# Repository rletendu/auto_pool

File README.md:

# AutoPool

ESP32 swimming-pool controller with pH / ORP / filter automation, Nextion touch UI, web dashboard, MQTT, and native Home Assistant autodiscovery.

AutoPool runs unattended on the side of the pool: it schedules the filter pump, doses chlorine on ORP, holds pH inside a target band by injecting acid (and optionally base) through peristaltic pumps, watches tank levels, and exposes everything over a 5″ touch panel, a web UI, and MQTT.

---

## Table of contents

- [Features](#features)
- [Hardware](#hardware)
- [Architecture](#architecture)
- [Build, flash and first boot](#build-flash-and-first-boot)
- [Configuration](#configuration)
- [Winter mode](#winter-mode)
- [MQTT](#mqtt)
- [Home Assistant integration](#home-assistant-integration)
- [Web UI and Nextion display](#web-ui-and-nextion-display)
- [OTA, CLI and Telnet](#ota-cli-and-telnet)
- [ESPHome alternative](#esphome-alternative)
- [Repository layout](#repository-layout)
- [Credits and license](#credits-and-license)

---

## Features

**Regulation**
- Filter pump scheduling — 24-hour fixed bitmap or per-temperature program (selected by `filter_auto_mode`)
- Filter speed control (FULL / REG) on a variable-speed pump
- Periodic short-cycle filter run for stagnation prevention
- **Winter mode** — short winter filter program, frost protection driven by an outdoor temperature pushed by Home Assistant, chemistry locked OFF (see [Winter mode](#winter-mode))
- pH minus (and optional pH plus) dosing on a fixed regulation cycle, proportional to deviation from target
- ORP / chlorine dosing on a fixed regulation cycle with daily mL caps
- Daily injection counters with automatic midnight reset (preserved across soft resets via RTC slow memory)

**Sensing**
- DS18B20 — water temperature (OneWire)
- DHT22 — air temperature and humidity inside the enclosure
- ADS1115 — pH probe, ORP probe, and pump-loop pressure transducer (3 channels)
- DS3231 — battery-backed RTC
- Four float switches — water level + Cl / pH- / pH+ tank levels

**Interfaces**
- Nextion 5″ resistive touch panel (`hmi/auto_pool_ui.HMI`)
- Responsive web dashboard served from SPIFFS (`http://<ip>/`)
- MQTT — measures, states, parameters, log, command, with **Home Assistant autodiscovery** (~40 entities) and LWT availability
- Serial CLI (`SimpleCLI`)
- OTA — firmware, SPIFFS filesystem, and Nextion display

---

## Hardware

The full schematic and PCB live in [`hardware/`](hardware/):

- [`hardware/autopool.pdf`](hardware/autopool.pdf) — schematic
- [`hardware/autopool.kicad_pcb`](hardware/autopool.kicad_pcb) — KiCad PCB
- [`hardware/autopool.png`](hardware/autopool.png), [`autopool_3.png`](hardware/autopool_3.png) — board renders
- [`3D/`](3D/) — printable enclosure parts (STL / STEP)

### Bill of materials (top level)

| Block | Part |
|---|---|
| MCU | ESP32 dev module |
| Display | Nextion 5″ (NX8048T050 or compatible) |
| Analog frontend | ADS1115 (I²C) for pH / ORP / pressure |
| RTC | DS3231 (I²C, battery-backed) |
| Air sensor | DHT22 |
| Water sensor | DS18B20 (OneWire) |
| Filter pump driver | Solid-state relay (active-high) |
| Dosing | 3× peristaltic pumps (Cl, pH-, pH+) on relays (active-low) |
| Levels | 4× float switches (water, Cl, pH-, pH+) |
| Misc | Piezo buzzer, two status LEDs |

### Pin map (excerpt, see [`src/board.h`](src/board.h) for the source of truth)

| Function | GPIO | Notes |
|---|---|---|
| Filter pump SSR | `PIN_EXT1` (14) | active **high** (`PUMP_FILTER_ACTIVE_VALUE = true`) |
| Filter speed (FULL/REG) | `PIN_EXT2` (15) | optional, gated by `HAS_FILTER_PWR_CTRL` |
| Cl pump relay | 25 | active **low** (`PUMP_ACTIVE_VALUE = false`) |
| pH- pump relay | 32 | active low |
| pH+ pump relay | 4 | active low, gated by `HAS_PH_PLUS_PUMP` |
| DS18B20 (water temp) | 13 | OneWire |
| DHT22 | 18 | |
| I²C (ADS1115, DS3231) | 21 / 22 | SDA / SCL |
| Nextion display | 16 / 17 | `Serial2` RX / TX, 115 200 baud |
| Float switches | 34, 35, 36, 39 | water / Cl / pH- / pH+ (input-only pins) |
| Buzzer | 5 | |

> **Polarity matters.** The filter pump SSR is wired through `PIN_EXT1` and is active-high; the dosing relays are active-low. Always go through the helpers in `board.h` (`pump_filtration_on/off`, `pump_ph_minus_on/off`, …) — never `digitalWrite` directly from feature code.

---

## Architecture

```
                    ┌────────────────────────┐
                    │       main.cpp         │
                    │  setup() / loop()      │
                    └──────────┬─────────────┘
                               │ SoftTimer ticks
        ┌──────────────┬───────┴───────┬──────────────┐
        ▼              ▼               ▼              ▼
  filter_control   ph_control     orp_control     measures
   (state machine) (state machine)(state machine) (sensor reads)
        │              │               │              │
        └────────┬─────┴────────┬──────┴──────┬───────┘
                 ▼              ▼             ▼
              board.h        state.h     parameters.h
            (HW helpers)   (live state)  (persisted setpoints)
                 │              │             │
                 ▼              ▼             ▼
        ┌────────────────────────────────────────────┐
        │   display  │  mqtt  │  server  │  cli  │ ota │
        └────────────────────────────────────────────┘
```

- **Cooperative scheduling** — every subsystem registers periodic work on a [`SoftTimer`](src/soft_timer.h) instance; no `delay()` in the main loop.
- **Three regulators** with explicit state machines defined in [`src/state.h`](src/state.h):
  - `filter_control_state_t` — IDLE → WARM_UP → ACTIVE → EXTENDED → PERIODIC, plus FROST (winter-mode frost protection)
  - `ph_control_state_t` — IDLE / MINUS_INJECTION_{ON,OFF} / PLUS_INJECTION_{ON,OFF}
  - `orp_control_state_t` — IDLE / INJECTION_{ON,OFF}
- **Persistence** — two SPIFFS JSON files in [`data/`](data/):
  - `/config.json` ↔ `ParametersStruture` ([`src/parameters.h`](src/parameters.h))
  - `/state.json` ↔ last-known mode of each regulator, winter mode and the pre-winter chemistry modes (so a reboot does not reset operator intent)
- **Compile-time feature gates** in [`src/config.h`](src/config.h): `HAS_PH_CONTROL`, `HAS_ORP_CONTROL`, `HAS_FILTER_CONTROL`, `HAS_FILTER_PWR_CTRL`, `HAS_PH_PLUS_PUMP`, `HAS_MQTT`, `HAS_OTA`, `HAS_WEB_SERVER`, `HAS_CLI`, `HAS_TELNET_SERVER`, `HAS_QUIET_MEASURES`, `HAS_CUSTOM_MAC`.

---

## Build, flash and first boot

PlatformIO is the only toolchain. The single environment is `esp32dev`, defined in [`platformio.ini`](platformio.ini).

```bash
# Build
pio run

# Flash firmware over USB
pio run -t upload

# Flash firmware OTA
pio run -t upload --upload-port 192.168.x.x

# Flash the SPIFFS filesystem (web UI + config.json + state.json)
# Required after editing anything under data/
pio run -t uploadfs

# Serial monitor at 115 200 baud
pio device monitor

# Clean build
pio run -t clean
```

> **Firmware vs. filesystem are two independent flashes.** `pio run -t upload` writes the application binary (everything compiled from `src/`); `pio run -t uploadfs` writes the SPIFFS image built from `data/` (web UI, `config.json`, `state.json`). They're independent partitions on the ESP32 — flashing one never touches the other. Rules of thumb:
>
> - **Edited C/C++ in `src/` or `lib/`** → `pio run -t upload`. No `uploadfs` needed; settings and web assets are untouched.
> - **Edited anything under `data/`** (web UI, default `config.json`) → `pio run -t uploadfs`. No firmware reflash needed.
> - **Both** → run them in either order; e.g. `pio run -t upload && pio run -t uploadfs`.
> - **OTA**: both targets accept `--upload-port <ip>` to flash over Wi-Fi via `espota`, e.g. `pio run -t uploadfs --upload-port 192.168.x.x`.
> - **Heads up on `uploadfs`**: it rewrites the whole SPIFFS partition, including `config.json` **and** `state.json`. Settings changed via the web UI / portal / MQTT are lost, and the default `data/state.json` puts pH / ORP back in AUTO, drops winter mode and resets the total filter runtime. Pull the live config back first (`curl http://<ip>/getparameters > data/config.json`) if you want to preserve it.
> - **Updating only the web UI** on a running controller: skip `uploadfs` and push the changed files through the built-in file upload endpoint, which leaves `config.json` / `state.json` alone:
>   ```bash
>   for f in index.html app.js settings.html settings.js style.css; do
>     curl -F "file=@data/$f;filename=/$f" http://<ip>/edit
>   done
>   ```

> **There are no unit tests** wired up. `test/autopool_tester.py` is a host-side helper, not a PlatformIO test runner.

### First boot

On first power-up the device opens a captive Wi-Fi portal named **`AUTOPOOL_CONFIG`**. Connect to it and configure:

- Wi-Fi SSID / password
- MQTT server / port / user / password
- MQTT base topic (default: `autopool`)

Settings persist to `/config.json` on SPIFFS. To re-trigger the portal later, send the `portal` CLI command on the serial console, or hit `/reboot` after wiping settings via `portal_reset`.

---

## Configuration

Three editing channels feed the same [`ParametersStruture`](src/parameters.h):

1. **Web UI** — `http://<ip>/settings.html` (form is bound by [`data/settings.js`](data/settings.js))
2. **MQTT** — publish a full JSON payload to `<base>/CMD/PARAMETERS`, or update one field at a time with `<base>/CMD/SET/<KEY>` *(see [MQTT](#mqtt))*
3. **WiFiManager portal** — for the network and broker fields only, on first boot or after `portal` / `portal_reset`

### Most-edited parameters

| Field | Meaning | Typical |
|---|---|---|
| `target_ph`, `delta_ph` | pH setpoint and dead-band | 7.4 ± 0.15 |
| `target_orp`, `delta_orp` | ORP setpoint (mV) and dead-band | 650 ± 70 |
| `flow_cl`, `flow_ph_minus`, `flow_ph_plus` | Peristaltic pump flow rate (mL/min) | 25 |
| `cl_max_day`, `phm_max_day` | Daily injection caps (mL) | 2000 |
| `pressure_warning` | Filter loop alarm threshold (bar) | 1.9 |
| `ph_offset`, `orp_offset` | Probe calibration offsets | 0 |
| `timer_prog` | 24-bit hourly bitmap for filter run | — |
| `filter_auto_mode` | `0` = bitmap, `1` = function of water temperature | 0 |
| `timer_prog_temperature[11]` | Per-temperature bitmaps (10 °C → 30 °C, step 2 °C) | — |
| `periodic_filter_time` | Minutes between short anti-stagnation cycles (0 disables) | 0 |
| `winter_start_hour`, `winter_duration_h` | Winter filter window (start hour, length in hours, wraps past midnight) | 4, 3 |
| `frost_threshold` | Outdoor temperature (°C) that starts frost protection in winter mode | 1.0 |
| `ha_discovery_enabled`, `ha_discovery_prefix` | HA autodiscovery toggle and topic prefix | `false`, `homeassistant` |

---

## Winter mode

An *active* wintering mode: the water stays in the pool, the filter runs a short daily window and protects the pipes from freezing. It is toggled from Home Assistant (`switch.autopool_winter_mode`), the web dashboard, or MQTT `SET/WINTER_MODE`, and persists across reboots. The Nextion HMI is unchanged: it shows the winter program in the timer grid and the events on the LOG page.

While winter mode is on:

- **Filtration** — the AUTO program is replaced by `winter_duration_h` hours starting at `winter_start_hour` (default 04:00–07:00). `filter_auto_mode` and `timer_prog` are left untouched and apply again when winter mode ends.
- **Chemistry** — pH-, pH+ and ORP are forced OFF; any request to switch them back on (Nextion, MQTT, web, CLI) is refused and logged. Their previous modes are saved and restored when winter mode ends.
- **Frost protection** — in filter AUTO, the pump runs continuously (filter state `FROST`) when the outdoor temperature drops to `frost_threshold`, and stops 1.5 °C above it.
  - The outdoor temperature is pushed by Home Assistant to `<base>/CMD/OUTDOOR_TEMP`. A value older than 30 min is ignored, and the controller falls back to the water temperature (frost below 4 °C, cleared above 5 °C).
  - The enclosure DHT22 is **not** used: it reads the temperature inside the box.
  - A manual filter **OFF** always wins (maintenance): the pump is not started, but `frost_alert` is raised instead.

Home Assistant has to feed the outdoor temperature. An automation such as the following works: every 10 minutes and on each change, it publishes the coldest of a garden sensor and the weather forecast.

```yaml
alias: AutoPool – Outdoor temperature
mode: queued
triggers:
  - trigger: state
    entity_id: sensor.garden_temperature
  - trigger: state
    entity_id: weather.home
    attribute: temperature
  - trigger: time_pattern
    minutes: /10
  - trigger: homeassistant
    event: start
variables:
  outdoor_temps: >-
    {{ [states('sensor.garden_temperature'), state_attr('weather.home', 'temperature')]
       | select('is_number') | map('float') | list }}
conditions:
  - condition: template
    value_template: "{{ outdoor_temps | count > 0 }}"
actions:
  - action: mqtt.publish
    data:
      topic: autopool/CMD/OUTDOOR_TEMP
      payload: "{{ outdoor_temps | min | round(1) }}"
```

---

## MQTT

All topics are rooted at `<base>` (the value of `mqtt_base_topic`, default `autopool`).

### Published

| Topic | Retained | Payload |
|---|---|---|
| `<base>/AVAIL` | yes | `online` while the controller is up; `offline` published as LWT on disconnect |
| `<base>/MEAS` | no | JSON snapshot of [`MeasuresStructure`](src/measures.h) (temps, pH, ORP, pressure, levels, daily mL counters, filter runtime, boot count). `water_temperature` is omitted until the first valid reading after boot, and `outdoor_temperature` while it is stale |
| `<base>/STATE_FILTER` | no | JSON snapshot of the filter regulator state, including `winter_mode`, `frost_active`, `frost_alert` |
| `<base>/STATE_PH` | no | JSON snapshot of the pH± regulator state |
| `<base>/STATE_ORP` | no | JSON snapshot of the ORP regulator state |
| `<base>/PARAM` | no | Echo of the current `ParametersStruture` after any change |
| `<base>/LOG`, `<base>/DEBUG` | no | Free-form text |
| `<prefix>/+/autopool_<mac>/+/config` | yes | HA discovery configs (only when `ha_discovery_enabled` is set) |

### Subscribed (`<base>/CMD/<KEY>`)

**Mode commands** *(legacy string suffix, empty payload):*
`FILTER_MODE_AUTO` · `FILTER_MODE_ON` · `FILTER_MODE_OFF` · `FILTER_PWR_FULL` · `FILTER_PWR_REG` · `ORP_MODE_AUTO` · `ORP_MODE_ON` · `ORP_MODE_OFF`

**Per-field SET commands** *(payload = scalar value, suitable for HA selects/numbers):*

| Topic | Payload |
|---|---|
| `SET/FILTER_MODE` | `AUTO` \| `ON` \| `OFF` |
| `SET/FILTER_POWER` | `FULL` \| `REG` |
| `SET/ORP_MODE` | `AUTO` \| `ON` \| `OFF` |
| `SET/PH_MINUS_MODE` | `AUTO` \| `ON` \| `OFF` |
| `SET/PH_PLUS_MODE` | `AUTO` \| `ON` \| `OFF` |
| `SET/TARGET_PH`, `SET/DELTA_PH` | float |
| `SET/TARGET_ORP`, `SET/DELTA_ORP` | float (mV) |
| `SET/FLOW_CL`, `SET/FLOW_PH_MINUS`, `SET/FLOW_PH_PLUS` | float (mL/min) |
| `SET/CL_MAX_DAY`, `SET/PHM_MAX_DAY` | float (mL) |
| `SET/PRESSURE_WARNING` | float (bar) |
| `SET/PH_OFFSET`, `SET/ORP_OFFSET` | float (calibration) |
| `SET/PERIODIC_FILTER_TIME` | minutes |
| `SET/WINTER_START_HOUR`, `SET/WINTER_DURATION_H` | integer (hour 0–23, hours 0–24) |
| `SET/FROST_THRESHOLD` | float (°C) |

Per-field SET commands persist to `/config.json` and echo on `<base>/PARAM`.

**Winter mode:**

| Topic | Payload |
|---|---|
| `SET/WINTER_MODE` | `ON` \| `OFF` — persisted in `/state.json` |
| `OUTDOOR_TEMP` | float (°C), pushed periodically by HA; volatile, stale after 30 min |

**JSON updates** *(payload = full JSON document):*
`PARAMETERS` · `MEASURES` · `FILTER_STATE` · `ORP_STATE` · `PH_STATE`

**Utility:** `RESET` · `RST_DAILY_ML_ORP` · `BEEP` · `GET_PARAMETERS` · `GET_STATES` · `LOG` · `FS`

---

## Home Assistant integration

Two paths, pick one.

### Autodiscovery (recommended)

1. Open the AutoPool web UI → **Settings** → tick **Enable autodiscovery**, leave the prefix as `homeassistant` unless your HA instance uses a custom one.
2. Click **Submit**. The controller publishes ~55 retained discovery configs under `<prefix>/+/autopool_<mac>/+/config`.
3. Home Assistant's MQTT integration picks them up automatically. AutoPool appears as a single device with:
   - Sensors — water / system temperature, humidity, pressure, pH, ORP, daily mL counters, boot count
   - Binary sensors — water level, three tank levels, four pump-running indicators
   - Selects — filter mode, filter power, ORP mode, pH± modes
   - Switch — winter mode
   - Binary sensors — frost protection running, frost alert
   - Sensor — outdoor temperature as received from HA (diagnostic)
   - Numbers — every setpoint listed in [Configuration](#configuration), including the winter settings
   - Buttons — controller reset, daily Cl counter reset, boot counter reset
   - Diagnostic sensors — internal state of the three regulators
4. To remove the device: untick the checkbox; the controller publishes empty retained payloads to clear every discovery topic.

The companion dashboard at [`homeassistant/dashboards/autopool.yaml`](homeassistant/dashboards/autopool.yaml) is wired entirely to the autodiscovered entity_ids (`<domain>.autopool_<object>`, courtesy of the `obj_id` field in each discovery payload). It uses only stock Lovelace cards — no HACS install required. Drop it under `<HA_config>/dashboards/` and register it via the `lovelace.dashboards` block in [`homeassistant/configuration_snippet.yaml`](homeassistant/configuration_snippet.yaml).

### Multi-device deployment

Two AutoPool controllers can share a single MQTT broker and a single Home Assistant instance. Set `device_suffix` on each one — short, lowercase, `[a-z0-9_]`, max 12 chars (e.g. `north`, `south`, `pool1`). The suffix is spliced into:

| Identifier | Empty suffix | Suffix `north` |
|---|---|---|
| MQTT `client_id` | `AUTOPOOL` | `AUTOPOOL_north` |
| HA `obj_id` (entity_id slug) | `autopool_<object>` | `autopool_north_<object>` |
| HA device name | `AutoPool` | `AutoPool north` |
| WiFiManager portal SSID | `AUTOPOOL_CONFIG` | `AUTOPOOL_CONFIG_north` |
| OTA mDNS hostname | `autopool.local` | `autopool-north.local` |

`mqtt_base_topic` is also auto-rewritten when you set the suffix via `<base>/CMD/SET/DEVICE_SUFFIX` (and only if the topic still has the legacy default `autopool` / empty). Set it manually otherwise via the WiFi portal or web UI to keep the two devices on disjoint topic trees.

Caveats:
- The very first portal setup of a fresh unit always uses the legacy SSID `AUTOPOOL_CONFIG` (suffix is set inside the portal itself). Configure both units sequentially the first time, not simultaneously.
- After changing a non-empty suffix, HA's old entities go to *unavailable* until the next HA restart — the controller publishes empty retained payloads to the old discovery topics so they age out cleanly.
- The supplied dashboard at [`homeassistant/dashboards/autopool.yaml`](homeassistant/dashboards/autopool.yaml) targets a single device with empty suffix. For multi-device dashboards, copy the file and `sed 's/autopool_/autopool_<suffix>_/g'` to retarget.

### Manual packages (legacy)

If you'd rather not run discovery, the older path still works: copy [`homeassistant/packages/autopool.yaml`](homeassistant/packages/autopool.yaml) and [`homeassistant/custom_templates/autopool.jinja`](homeassistant/custom_templates/autopool.jinja) into your HA config, enable `packages: !include_dir_named packages` in `configuration.yaml`, and **disable** the autodiscovery toggle on the controller — running both at once creates duplicate entities. The header of `packages/autopool.yaml` documents the migration trade-offs.

---

## Web UI and Nextion display

### Web UI

| Dashboard | Settings |
| --- | --- |
|  |  |

The dashboard is responsive and works the same on a phone:

Served by [`src/server.cpp`](src/server.cpp) from SPIFFS:

- `/` — live dashboard (measures, daily counters, regulator modes, winter mode and frost status)
- `/settings.html` — full configuration form
- `/getmeasures`, `/getparameters`, `/getfilterstate`, `/getorpstate`, `/getphstate` — JSON endpoints used by the dashboard
- `/setparameters` — POST endpoint backing the settings form
- `/filter_auto`, `/filter_on`, `/filter_off`, `/filter_pwr_full`, `/filter_pwr_reg`, `/orp_*`, `/ph_*`, `/winter_on`, `/winter_off` — quick-action buttons
- `/reboot`, `/rst_daily_ml_orp` — maintenance
- `/edit`, `/list`, `/fs` — SPIFFS file browser

### Nextion display

- HMI source: [`hmi/auto_pool_ui.HMI`](hmi/auto_pool_ui.HMI) (open in Nextion Editor)
- Pre-built TFT firmware lives under [`hmi/tft/`](hmi/tft/) — flash directly from an SD card, or push over the air via [`src/ota_tft.cpp`](src/ota_tft.cpp) (uses [`lib/ESPNexUpload`](lib/ESPNexUpload))
- Display drives `Serial2` (`PIN_RX2 = 16`, `PIN_TX2 = 17`) at 115 200 baud
- Firmware references widgets by name in [`src/display_components.cpp`](src/display_components.cpp); add new touch callbacks in [`src/display.cpp`](src/display.cpp)

---

## OTA, CLI and Telnet

- **Firmware OTA** — ArduinoOTA, invoked via `pio run -t upload --upload-port <ip>`
- **Filesystem OTA** — same syntax with `-t uploadfs`
- **Display OTA** — streamed by `ESPNexUpload`, triggered from the web UI / MQTT
- **Serial CLI** — three commands today (parsed by `SimpleCLI` in [`src/cli.cpp`](src/cli.cpp)):
  - `portal` — open the Wi-Fi captive portal and reboot
  - `portal_reset` — wipe Wi-Fi credentials and reboot
  - `format` — format SPIFFS (destructive)
- **Telnet** — off by default (`HAS_TELNET_SERVER 0` in [`src/config.h`](src/config.h)); flips on a `RemoteDebug` server when enabled

---

## ESPHome alternative

[`autopool_esphome.yaml`](autopool_esphome.yaml) is a parallel, in-progress port of the same hardware to ESPHome. The PlatformIO firmware in [`src/`](src/) remains the authoritative implementation. Migration notes / design log: [`2026-04-24-migration_esphome.txt`](2026-04-24-migration_esphome.txt). Secrets for the ESPHome flavour go in `secrets.yaml` (gitignored).

---

## Repository layout

```
src/                   Firmware (Arduino / PlatformIO) — main.cpp + per-subsystem modules
data/                  SPIFFS payload (web UI, config.json, state.json)
lib/                   Vendored libraries: Nextion, WiFiManager, RemoteDebug, SerialDebug, ESPNexUpload
hardware/              KiCad schematic, PCB, renders, gerbers
3D/                    Enclosure parts (STL / STEP)
hmi/                   Nextion HMI source + compiled .tft + assets
homeassistant/         Drop-in HA packages, dashboard, Jinja templates, integration snippet
autopool_esphome.yaml  Experimental ESPHome rewrite
platformio.ini         Build config (single env: esp32dev)
CLAUDE.md              Architecture / contributor guide (also used by AI assistants)
```

---

## Credits and license

Author: **Raphaël Letendu** — [github.com/rletendu/auto_pool](https://github.com/rletendu/auto_pool).

Vendored library licenses live alongside each library under [`lib/*/LICENSE*`](lib/). The repository does not currently carry a top-level `LICENSE` file; if you intend to publish the firmware, add one (MIT or GPL-2.0+ are common picks for ESP32 hobby projects).

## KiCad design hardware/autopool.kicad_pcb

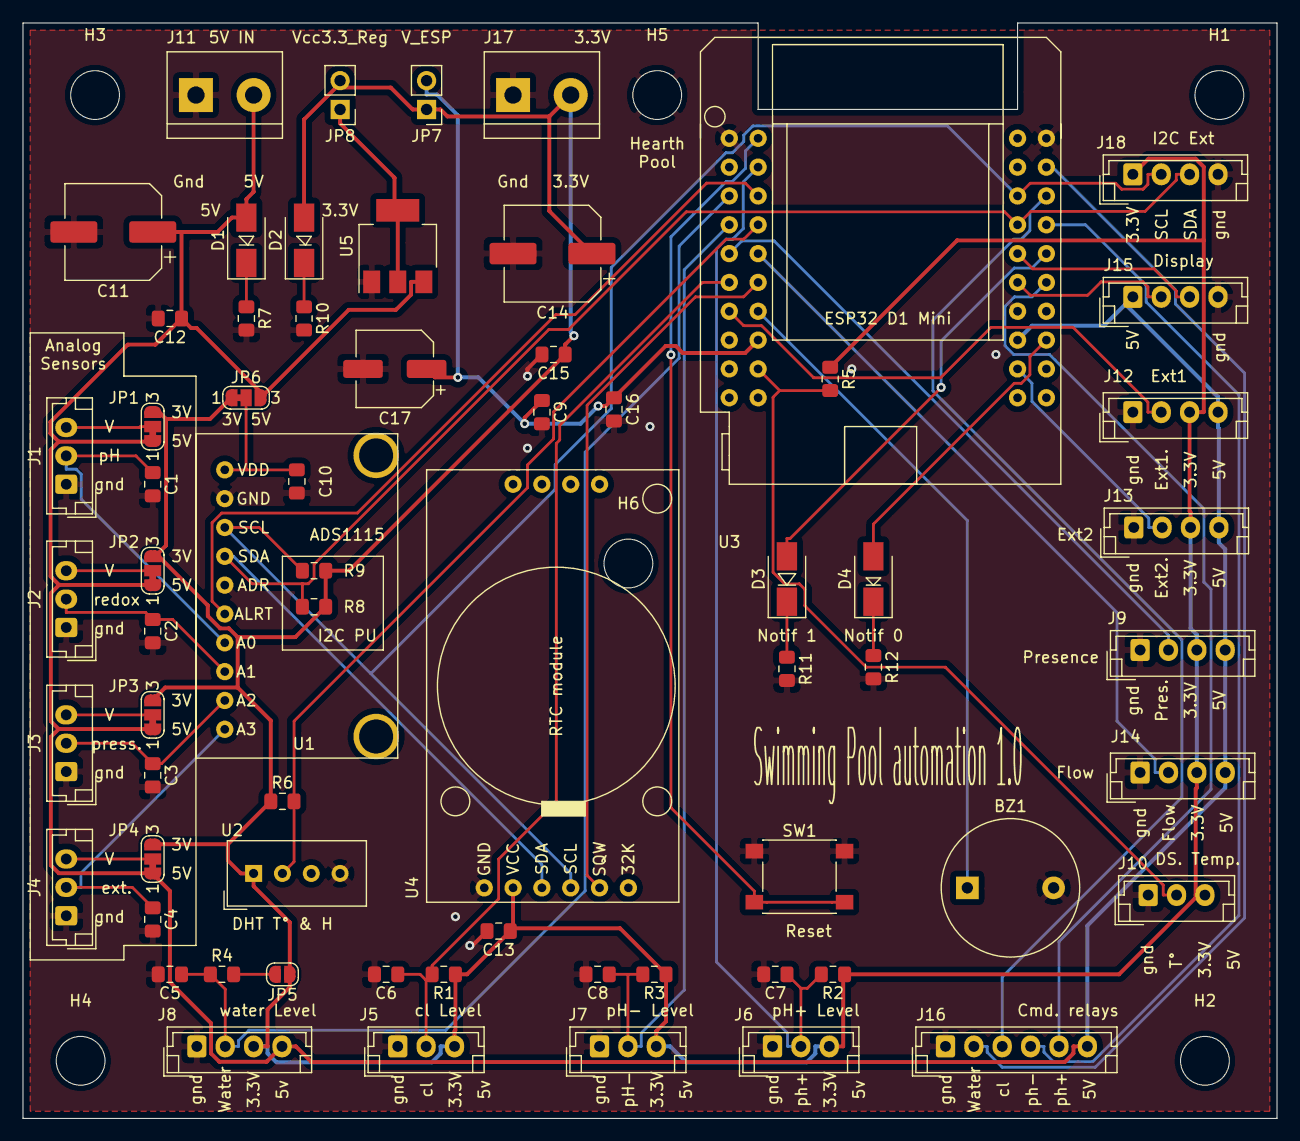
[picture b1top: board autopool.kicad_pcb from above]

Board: 2 copper layers, 110.5 x 96.5 mm, 72 parts (0 on the bottom side), 43 nets.

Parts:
BZ1: Buzzer; Buzzer_12x9.5RM7.6
C1, C2, C3, C4, C5, C6, C7, C8: 100p; C_0805_2012Metric_Pad1.15x1.40mm_HandSolder
C9, C10, C12, C13, C15: 100n; C_0805_2012Metric_Pad1.15x1.40mm_HandSolder
C11, C14: 47u; CP_Elec_8x11.9
C16: 1u; C_0805_2012Metric_Pad1.15x1.40mm_HandSolder
C17: 10u; CP_Elec_6.3x9.9
D1: 5.5V; D_SMA
D2: 3.3V; D_SMA
D3: Notif1; D_SMA
D4: Notif0; D_SMA
H1, H2, H3, H4, H5, H6: MountingHole_Pad; MountingHole_4.3mm_M4
J1: pH Sense; JST_EH_B3B-EH-A_1x03_P2.50mm_Vertical
J2: Cl Sense; JST_EH_B3B-EH-A_1x03_P2.50mm_Vertical
J3: Pressure. Sense; JST_EH_B3B-EH-A_1x03_P2.50mm_Vertical
J4: Extra Sense; JST_EH_B3B-EH-A_1x03_P2.50mm_Vertical
J5: Cl LevelMin; JST_EH_B3B-EH-A_1x03_P2.50mm_Vertical
J6: pH+ LevelMin; JST_EH_B3B-EH-A_1x03_P2.50mm_Vertical
J7: pH- LevelMin; JST_EH_B3B-EH-A_1x03_P2.50mm_Vertical
J8: Water_level; JST_EH_B4B-EH-A_1x04_P2.50mm_Vertical
J9: Presence; JST_EH_B4B-EH-A_1x04_P2.50mm_Vertical
J10: Water_temp; JST_EH_B3B-EH-A_1x03_P2.50mm_Vertical
J11: VCC_5V; TerminalBlock_bornier-2_P5.08mm
J12: Ext1; JST_EH_B4B-EH-A_1x04_P2.50mm_Vertical
J13: Ext2; JST_EH_B4B-EH-A_1x04_P2.50mm_Vertical
J14: Flow; JST_EH_B4B-EH-A_1x04_P2.50mm_Vertical
J15: Display; JST_EH_B4B-EH-A_1x04_P2.50mm_Vertical
J16: Relays; JST_EH_B6B-EH-A_1x06_P2.50mm_Vertical
J17: VCC_3.3V; TerminalBlock_bornier-2_P5.08mm
J18: I2C_est1; JST_EH_B4B-EH-A_1x04_P2.50mm_Vertical
JP1: V_pH; SolderJumper-3_P1.3mm_Bridged12_RoundedPad1.0x1.5mm_NumberL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
JP2: V_cl; SolderJumper-3_P1.3mm_Bridged12_RoundedPad1.0x1.5mm_NumberL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
JP3: V_Press.; SolderJumper-3_P1.3mm_Bridged12_RoundedPad1.0x1.5mm_NumberL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
JP4: V_extra; SolderJumper-3_P1.3mm_Bridged12_RoundedPad1.0x1.5mm_NumberL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
JP5: pu_water; SolderJumper-2_P1.3mm_Open_RoundedPad1.0x1.5mm
JP6: V_ads; SolderJumper-3_P1.3mm_Bridged12_RoundedPad1.0x1.5mm_NumberL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
JP7: vccESP; PinHeader_1x02_P2.54mm_Vertical
JP8: VCC_33; PinHeader_1x02_P2.54mm_Vertical
R1, R2, R3, R4, R5, R6: 10k; R_0805_2012Metric_Pad1.15x1.40mm_HandSolder
R7: 470; R_0805_2012Metric_Pad1.15x1.40mm_HandSolder
R8, R9: 2.2k; R_0805_2012Metric_Pad1.15x1.40mm_HandSolder
R10, R11, R12: 330; R_0805_2012Metric_Pad1.15x1.40mm_HandSolder
SW1: Reset; SW_Push_1P1T_NO_6x6mm_H9.5mm
U1: ADS1115_module
U2: DHT11; Aosong_DHT11_5.5x12.0_P2.54mm
U3: ESPMINI32; esp32_mini
U4: RTC_DS3231_MODULE; RTC_DS3231_MODULE_H
U5: AMS1117-3.3; SOT-223-3_TabPin2

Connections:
+3V3: C13.1, C14.1, C15.1, D2.2, J5.3, J6.3, J7.3, J8.3, J9.3, J10.3, J12.3, J13.3, J14.3, J17.2, J18.1, JP1.3, JP2.3, JP3.3, JP4.3, JP5.1, JP6.1, JP7.1, JP8.2, R1.1, R2.1, R3.1, R5.1, R6.1, R8.1, R9.1, U2.1, U4.2
+5V: C11.1, C12.1, D1.2, J8.4, J9.4, J11.2, J12.4, J13.4, J14.4, J15.1, J16.6, JP1.1, JP2.1, JP3.1, JP4.1, JP6.3, U3.28, U5.3
/3.3_esp: C9.1, C16.1, C17.1, JP7.2, U3.18
/3V3_reg: JP8.1, U5.2
/Cl: C2.1, J2.2, U1.8
/Press: C3.1, J3.2, U1.9
/adc_alrt: U1.6, U3.13
/buzzer: BZ1.1, U3.17
/dht: R6.2, U2.2, U3.14
/ext1: J12.2, U3.7
/ext2: J13.2, U3.29
/extra: C4.1, J4.2, U1.10
/flow: J14.2, U3.15
/led0: D4.2, U3.38
/led1: D3.2, U3.35
/levelmin_cl: C6.1, J5.2, R1.2, U3.6
/levelmin_ph+: C7.1, J6.2, R2.2, U3.12
/levelmin_ph-: C8.1, J7.2, R3.2, U3.4
/levelmin_water: C5.1, J8.2, R4.1, U3.3
/pH: C1.1, J1.2, U1.7
/presence: J9.2, U3.5
/pump_cl: J16.3, U3.33
/pump_ph+: J16.5, U3.36
/pump_ph-: J16.4, U3.34
/pump_water: J16.2, U3.32
/rtc_int: U3.16, U4.5
/rx2: J15.2, U3.26
/scl: J18.2, R9.2, U1.3, U3.23, U4.4
/sda: J18.3, R8.2, U1.4, U3.24, U4.3
/tx2: J15.3, U3.25
/water_temp: J10.2, R5.2, U3.19
GND: BZ1.2, C1.2, C2.2, C3.2, C4.2, C5.2, C6.2, C7.2, C8.2, C9.2, C10.2, C11.2, C12.2, C13.2, C14.2, C15.2, C16.2, C17.2, H5.1, J1.1, J2.1, J3.1, J4.1, J5.1, J6.1, J7.1, J8.1, J9.1, J10.1, J11.1, J12.1, J13.1, J14.1, J15.4, J16.1, J17.1, J18.4, R7.2, R10.2, R11.2, R12.2, SW1.1, U1.2, U1.5, U2.4, U3.1, U3.27, U3.31, U4.1, U5.1
unnamed: C10.1, JP6.2, U1.1
unnamed: D1.1, R7.1
unnamed: D2.1, R10.1
unnamed: D3.1, R11.1
unnamed: D4.1, R12.1
unnamed: J1.3, JP1.2
unnamed: J2.3, JP2.2
unnamed: J3.3, JP3.2
unnamed: J4.3, JP4.2
unnamed: JP5.2, R4.2
unnamed: SW1.2, U3.11

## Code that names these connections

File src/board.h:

#ifndef __BOARD_H__
#define __BOARD_H__

#include <Arduino.h>
#include "config.h"

#define PIN_LED0 2
#define PIN_LED1 12

#define PIN_RELAY_PUMP_PH_P 4
#define PIN_BUZZER 5

#define PIN_DS18B20 13
#define PIN_EXT1 14
#define PIN_EXT2 15

#define PIN_RX2 16
#define PIN_TX2 17

#define PIN_DISPLAY_RX PIN_RX2
#define PIN_DISPLAY_TX PIN_TX2

#define PIN_DHT 18

#define PIN_FLOW 19
#define PIN_SDA 21
#define PIN_SCL 22

#define PIN_RTC_INTERRUPT 23
#define PIN_RELAY_PUMP_CL 25

#define PIN_ADC_INTERRUPT 26

//#define PIN_RELAY_PUMP_FILTER 27
#define PIN_RELAY_PUMP_FILTER PIN_EXT1

#define PIN_RELAY_PUMP_PH_M 32

#ifndef PIN_PUMP_PWR
#define PIN_PUMP_PWR PIN_EXT2
#endif

#define PIN_PRESENCE 33

#define PIN_LEVEL_MIN_CL 34
#define PIN_LEVEL_MIN_PH_M 35
#define PIN_LEVEL_MIN_PH_P 36
#define PIN_LEVEL_MIN_WATER 39

#define ADS_CH_PH 0
#define ADS_CH_CL 1
#define ADS_CH_PRESSURE 2
#define ADS_CH_EXTRA 3

void board_init(void);

void pump_all_off(void);
void pump_ph_minus_on(void);
void pump_ph_minus_off(void);
void pump_ph_plus_on(void);
void pump_ph_plus_off(void);
void pump_ph_cl_on(void);
void pump_ph_cl_off(void);
void pump_filtration_on(void);
void pump_filtration_off(void);

#define PUMP_FILTER_ACTIVE_VALUE true
#define PUMP_FILTER_INACTIVE_VALUE ~PUMP_FILTER_ACTIVE_VALUE

#define PUMP_ACTIVE_VALUE false
#define PUMP_INACTIVE_VALUE ~PUMP_ACTIVE_VALUE

#define PUMP_PWR_FULL_VALUE 1
#define PUMP_PWR_REG_VALUE 0

#define LEVEL_WATER_OK_VALUE true
#define LEVEL_CL_OK_VALUE true
#define LEVEL_PH_MINUS_OK_VALUE true
#define LEVEL_PH_PLUS_OK_VALUE true

inline void led0_off(void) {digitalWrite(PIN_LED0, false);}
inline void led0_on(void) { digitalWrite(PIN_LED0, true); }
inline void led0_toggle(void) { digitalWrite(PIN_LED0, !digitalRead(PIN_LED0)); }
inline void led1_off(void) { digitalWrite(PIN_LED1, false); }
inline void led1_on(void) { digitalWrite(PIN_LED1, true); }
inline void led1_toggle(void) { digitalWrite(PIN_LED1, !digitalRead(PIN_LED1)); }

inline void pump_filtration_on(void) { digitalWrite(PIN_RELAY_PUMP_FILTER, PUMP_FILTER_ACTIVE_VALUE); }
inline void pump_filtration_off(void) { digitalWrite(PIN_RELAY_PUMP_FILTER, 0); }
inline bool pump_filtration_is_on(void) { return digitalRead(PIN_RELAY_PUMP_FILTER) == PUMP_FILTER_ACTIVE_VALUE ? true : false; }

#if HAS_FILTER_PWR_CTRL
inline void pump_filtration_pwr_full(void) { digitalWrite(PIN_PUMP_PWR, PUMP_PWR_FULL_VALUE); }
inline void pump_filtration_pwr_reg(void) { digitalWrite(PIN_PUMP_PWR, PUMP_PWR_REG_VALUE); }
#else 
inline void pump_filtration_pwr_full(void) {}
inline void pump_filtration_pwr_reg(void) {}
#endif

inline void pump_ph_minus_on(void) { digitalWrite(PIN_RELAY_PUMP_PH_M, PUMP_ACTIVE_VALUE); }
inline void pump_ph_minus_off(void) { digitalWrite(PIN_RELAY_PUMP_PH_M, PUMP_INACTIVE_VALUE); }
inline bool pump_ph_minus_is_on(void) { return digitalRead(PIN_RELAY_PUMP_PH_M) == PUMP_ACTIVE_VALUE ? true : false; }

inline void pump_ph_plus_on(void) { digitalWrite(PIN_RELAY_PUMP_PH_P, PUMP_ACTIVE_VALUE); }
inline void pump_ph_plus_off(void) { digitalWrite(PIN_RELAY_PUMP_PH_P, PUMP_INACTIVE_VALUE); }
inline bool pump_ph_plus_is_on(void) { return digitalRead(PIN_RELAY_PUMP_PH_P) == PUMP_ACTIVE_VALUE ? true : false; }

inline void pump_orp_on(void) { digitalWrite(PIN_RELAY_PUMP_CL, PUMP_ACTIVE_VALUE); }
inline void pump_orp_off(void) { digitalWrite(PIN_RELAY_PUMP_CL, PUMP_INACTIVE_VALUE); }
inline bool pump_cl_is_on(void) { return digitalRead(PIN_RELAY_PUMP_CL) == PUMP_ACTIVE_VALUE ? true : false; }

#ifdef DEBUG_PIN1
inline void debug_pin1_off(void) {  digitalWrite(DEBUG_PIN1, false); }
inline void debug_pin1_on(void) { digitalWrite(DEBUG_PIN1, true); }
inline void debug_pin1_toggle(void) { digitalWrite(DEBUG_PIN1, !digitalRead(DEBUG_PIN1)); }
#else
inline void debug_pin1_off(void) {  }
inline void debug_pin1_on(void) {  }
inline void debug_pin1_toggle(void) {  }
#endif

inline void pump_all_off(void)
{
	pump_filtration_off();
	pump_ph_minus_off();
	pump_ph_plus_off();
	pump_orp_off();
}

inline void buzzer_on(void) { digitalWrite(PIN_BUZZER, true); }
inline void buzzer_off(void) { digitalWrite(PIN_BUZZER, false); }

inline bool level_water_is_ok(void) { return digitalRead(PIN_LEVEL_MIN_WATER) == LEVEL_WATER_OK_VALUE ? true : false; }
inline bool level_cl_is_ok(void) { return digitalRead(PIN_LEVEL_MIN_CL) == LEVEL_CL_OK_VALUE ? true : false; }
inline bool level_ph_minus_is_ok(void) { return digitalRead(PIN_LEVEL_MIN_PH_M) == LEVEL_PH_MINUS_OK_VALUE ? true : false; }
inline bool level_ph_plus_is_ok(void) { return digitalRead(PIN_LEVEL_MIN_PH_P) == LEVEL_PH_PLUS_OK_VALUE ? true : false; }

void pump_filtration_off(void);

float dht_get_temperature(void);
float dht_get_humidity(void);
float rtc_get_temperature(void);
uint8_t ds18_count(void);
float ds18_get_temperature(uint8_t index);
float water_get_temperature(void);
float water_get_ph(void);
float water_get_orp(void);
float pump_filtration_get_pressure(bool store_offset);

bool rtc_set_time(struct tm time);

uint8_t rtc_get_hour(void);
uint8_t rtc_get_minute(void);
uint8_t rtc_get_second(void);
uint16_t rtc_get_year(void);
uint8_t rtc_get_month(void);
uint8_t rtc_get_day(void);

void beep(uint16_t ms);

#endif

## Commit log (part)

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2020-01-12 Gitignore
2020-01-12 Initial code
2020-01-13 More wip
2020-02-03 WIP board definition
2020-02-06 Fixig compilation errors
2020-02-08 Wip ,adding OTA
2020-02-10 Adding Nextion lib
2020-02-18 wip 1st board
2020-02-19 Adding display
2020-02-23 HMi init
2020-02-25 Display OTA
2020-02-25 Relays control
2020-02-25 pressure
2020-03-02 WIP MQTT
2020-03-02 WIP clean up
2020-03-05 Starting meausres
2020-03-06 Publishing parameters
2020-03-06 Adding regulation files
2020-03-06 NexXfloat.cpp
2020-03-08 Split component
2020-03-10 Wip & fix
2020-03-28 Split display ctrl fct
2020-03-29 First Relays ok
2020-03-30 HMI rebuilt
2020-03-30 Fixing CL level
2020-03-30 rtc display
2020-04-02 WIP json
2020-04-03 State mqtt
2020-04-05 Added logger
2020-04-05 Log adder
2020-04-06 wip log
2020-04-07 logger working
2020-04-09 reformating
2020-04-09 Auto stash before merge of "master" and "origin/master"
2020-04-10 Sleep attempt
2020-04-10 Fixing ctrl_prev
2020-04-14 DHT retry
2020-04-14 Main time update each minutes
2020-04-14 Buffer size
2020-04-14 Fixing float display
2020-04-14 wip rework ORP
2020-04-15 significant multi rework
2020-04-15 Not too bad
2020-04-16 fixing no-init counters
2020-04-17 First 3D
2020-04-19 New displly update
2020-04-19 Working with new display
2020-04-19 Fixing Display ORP / day size
2020-04-19 New logger
2020-04-20 WIP graph , DIM et screen saver
2020-04-20 fix screen saver delay
2020-04-21 wip fs
2020-04-21 Added channel clear
2020-04-21 disp_compute_graph_buffers
2020-04-21 adding 20pic fonts/ms20.zi
2020-04-21 Screen saver button
2020-04-21 Attempt to add TFT uploader
2020-04-21 Adding hardware info
2020-04-21 wip tft server update
2020-04-22 HMI adding ota_text visibility
2020-04-22 Cleanup
2020-04-26 Working dip OTA
2020-04-28 Massive clean up
2020-04-28 removing sleep and reset
2020-05-02 multiple fixes
2020-05-03 Good progress...
2020-05-06 wip html
2020-05-06 update default flow config
2020-05-11 Wip new server pages
2020-05-12 settings HTML
2020-05-14 Wip setparameters (not ok)
2020-05-15 Html working
2020-05-18 New IP + Fixed PH and CL levels
2020-05-25 Wip save state
2020-05-26 wip & TFT fix
2020-06-09 Fixing mqtt log
2020-06-10 Quiet measures as option
2020-06-23 UI: Added pump power button
2020-06-23 Added pump power components
2020-06-23 WIP pump power
2020-06-24 Wip pwr filer
2020-06-25 more filter power preparation
2020-06-28 HMI save ctrl button
2020-06-28 Added component save default
2020-06-29 Clean up + adding editor and file list
2020-07-01 Wip filter temperature mode
2020-07-01 Fixing timer prog
2020-07-02 Wip radio
2020-07-02 Added : periodic filter water safe temperature
2020-07-02 Fixing periodic
2020-07-03 Fixing parameter buffer ovf
2020-07-03 Added raw and max temp to status
2020-07-03 New hmi
2020-07-04 Split hours
2020-07-05 Comments clean up
2020-07-06 Added defaults config
2020-07-11 Change power full defaut
2020-07-17 Max ph correction to +/- 4
2020-07-19 Adding reboot , fixing filter reg
2023-01-05 2023 WIP rework
2024-05-05 forced arduino expressif to 2.0.10 for SPIFF
2024-05-06 2.0.13 as latest framework with SPIFF
2024-05-06 reset daily ml from server
2024-05-06 more MQTT commands
2024-05-06 counting orp daily while in force ON mode
2024-05-07 fixing log comments in PH control
2024-05-07 parameters.timer_prog = 0b111111111111000000000000;
2024-05-11 missing return
2024-05-11 adding config enable
2024-05-12 1.0 tentative
2024-09-01 moved filter pump realy to SSR (ext1 pin) changed polarity
2026-05-25 Change to HA MQTT
2026-05-28 Change to HA MQTT
    # Conflicts:
    # data/config.json
2026-05-28 Added claude.md and udpated toolchain
2026-05-29 Working ok
